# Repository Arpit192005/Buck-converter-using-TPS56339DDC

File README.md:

# Buck-converter-using-TPS56339DDC
Purpose: Converts 12 V DC input into a regulated 5 V DC output.
IC: TPS56339DDC, a synchronous buck converter with integrated MOSFETs.
Input connector (J1): Accepts 12 V DC power.
Input capacitors (C1, C2): Reduce input-voltage fluctuations and high-frequency noise.
Inductor (L1 – 5.6 µH): Stores and transfers energy to maintain a stable output.
Output capacitors (C4, C5 – 22 µF each): Reduce output ripple and help maintain voltage stability.
Feedback resistors (R1, R2): Set the output voltage to approximately 5 V.
Bootstrap network (30 Ω resistor and 100 nF capacitor): Supports the high-side MOSFET gate driver.
Output connector (J2): Delivers 5 V at up to 2 A continuous current.
Output power: 5 V × 2 A = 10 W.
Target ripple: ≤200 mV peak-to-peak, subject to simulation and hardware verification.

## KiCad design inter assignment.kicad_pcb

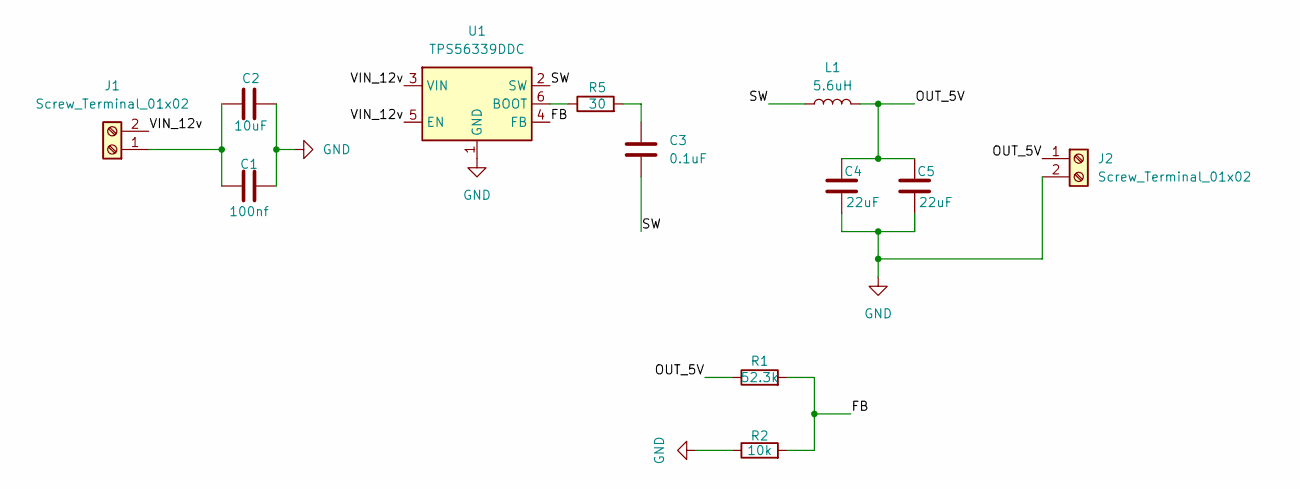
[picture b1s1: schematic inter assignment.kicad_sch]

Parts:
C1: 100nf; C_1825_4564Metric_Pad1.57x6.80mm_HandSolder
C2: 10uF; C_1825_4564Metric_Pad1.57x6.80mm_HandSolder
C3: 0.1uF; C_1825_4564Metric_Pad1.57x6.80mm_HandSolder
C4, C5: 22uF; C_1825_4564Metric_Pad1.57x6.80mm_HandSolder
J1, J2: Screw_Terminal_01x02; TerminalBlock_Phoenix_MKDS-1,5-2_1x02_P5.00mm_Horizontal
L1: 5.6uH; L_2512_6332Metric_Pad1.52x3.35mm_HandSolder
R1: 52.3k; R_Axial_DIN0309_L9.0mm_D3.2mm_P12.70mm_Horizontal
R2: 10k; R_Axial_DIN0309_L9.0mm_D3.2mm_P12.70mm_Horizontal
R5: 30; R_Axial_DIN0309_L9.0mm_D3.2mm_P12.70mm_Horizontal
U1: TPS56339DDC; SOT-23-6

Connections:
/FB: R1.2, R2.2, U1.4 (FB)
/OUT_5V: C4.1, C5.1, J2.1, L1.2, R1.1
/SW: C3.2, L1.1, U1.2 (SW)
/VIN_12v: J1.2, U1.3 (VIN), U1.5 (EN)
GND: C1.2, C2.2, C4.2, C5.2, J2.2, R2.1, U1.1 (GND)
unnamed: C3.1, R5.2
unnamed: C1.1, C2.1, J1.1
unnamed: R5.1, U1.6 (BOOT)

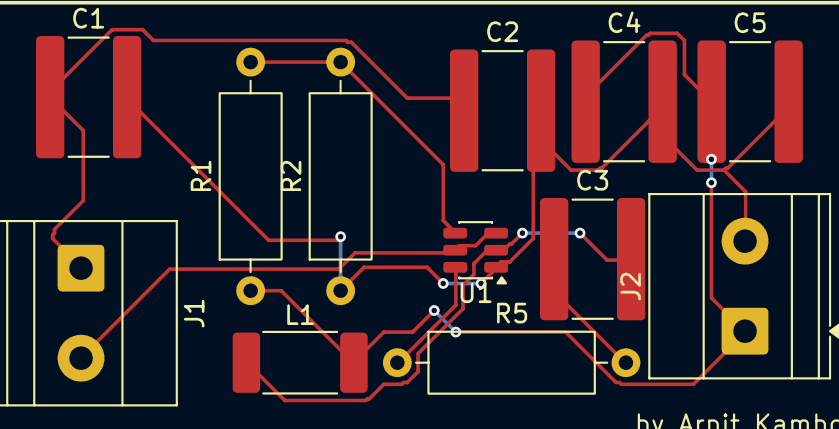
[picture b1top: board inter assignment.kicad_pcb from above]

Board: 2 copper layers, 12 parts (0 on the bottom side), 8 nets.
